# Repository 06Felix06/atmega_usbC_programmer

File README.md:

# ATmega USB-C Programmer

**A small USB-C tool for your own ATmega boards (ATmega328P, ATmega2560, ...). It burns the Arduino bootloader and uploads sketches through a single 2×4 pin header, so your PCBs don't need a USB chip.**

## The idea

If you design your own boards around a bare ATmega chip, for example the ATmega328P from the Arduino Uno/Nano or the ATmega2560 from the Arduino Mega, you normally have two annoying options:

- Put a full USB-to-serial circuit (CH340, USB connector, auto-reset) on **every** board. This costs space, money and adds more things that can go wrong.
- Or burn the bootloader with an Arduino Nano and a bunch of jumper wires, and then use a separate USB-serial adapter for every upload.

This programmer combines both jobs in one small device:

1. **Bootloader mode:** The programmer acts as an *Arduino as ISP* and burns the Arduino bootloader onto a brand-new ATmega through the SPI pins.
2. **Program mode:** The programmer's own microcontroller is switched out of the circuit, and the USB-serial converter is connected directly to the target chip. **Programmer + target board together behave exactly like a normal Arduino board** (for example a Nano with an ATmega328P or a Mega with an ATmega2560). You upload sketches and use the Serial Monitor as usual.

In other words, the Arduino is split in two: the USB part lives in the programmer, and the microcontroller lives on your board. All the target board needs is the ATmega, a resonator or crystal, a few capacitors and one 2×4 pin header.

Switching between the two modes takes four jumpers.

<p align="center"><em>A programmer in its 3D-printed case, plugged onto a second, freshly assembled programmer board to flash its bootloader</em></p>

## Supported microcontrollers

The programmer works with AVR chips that the Arduino IDE supports with a serial (UART) bootloader, for example:

| Target chip | Arduino board to select | Notes |
|---|---|---|
| ATmega328P | Arduino Nano or Arduino Uno | Most common case |
| ATmega2560 | Arduino Mega or Mega 2560 | Bootloader and uploads work the same way |

The programmer itself is always built around an ATmega328P, no matter which chip is on the target board.

## Features

- USB-C connector with a CH340C USB-to-serial converter
- ATmega328P-AU with 16 MHz resonator, running the standard *ArduinoISP* sketch
- One 8-pin connector to the target for both bootloader burning and code upload
- The programmer powers the target board with 5 V over the same connector
- Auto-reset over DTR, so uploads work just like on a regular Arduino board
- LEDs for power, RX, TX and a test LED
- Small 2-layer board (approx. 57 × 25 mm), all parts hand-solderable (0805, SOIC, TQFP)
- 3D-printable case with a window over the mode jumpers

## How it works

```mermaid
flowchart LR
    PC["PC<br/>(Arduino IDE)"] -- USB-C --> CH["CH340C<br/>USB-Serial"]
    CH -- "Bootloader mode<br/>TX / RX / DTR" --> MCU["Programmer ATmega328P<br/>(ArduinoISP)"]
    MCU -- "SPI: D11 / D12 / D13<br/>RESET: D10" --> T["Target ATmega328P<br/>(your board)"]
    CH -. "Program mode<br/>TX / RX / DTR" .-> T
```

The four 3-pin jumpers decide where the CH340's signals go:

| Jumper | Signal | Bootloader position | Program position |
|---|---|---|---|
| J3 | CH340 RXD | → programmer ATmega TX | → target TX |
| J4 | CH340 TXD | → programmer ATmega RX | → target RX |
| J5 | DTR auto-reset | → programmer ATmega RESET | → target RESET |
| J6 | Target RESET | ← programmer pin D10 (ISP reset) | ← DTR auto-reset (via J5) |

On the PCB, the **Bootloader** position is the two pins *away* from the square pad (pins 2–3) and the **Program** position is the two pins *next to* the square pad (pins 1–2). Always move all four jumpers together.

The SPI lines (programmer pins D11–D13) stay connected to the target in both modes. This is not a problem, because the ArduinoISP sketch keeps them as inputs whenever it isn't programming.

## Target connector pinout

Put this 2×4 male pin header (2.54 mm) on your own board. It has the same pinout and footprint as `J2` on the programmer, so the easiest way is to copy that footprint from the KiCad project.

```
          ┌───────────┬───────────┐
  pin 1 ● │ GND       │ RESET     │ pin 2
  pin 3   │ MOSI      │ SCK       │ pin 4
  pin 5   │ +5V       │ MISO      │ pin 6
  pin 7   │ TXD       │ RXD       │ pin 8
          └───────────┴───────────┘
```

Which chip pins these are depends on the target:

| Header signal | ATmega328P | ATmega2560 |
|---|---|---|
| MOSI | PB3 (D11) | PB2 (D51) |
| MISO | PB4 (D12) | PB3 (D50) |
| SCK | PB5 (D13) | PB1 (D52) |
| TXD | PD1 (D1) | PE1 (D1, TXD0) |
| RXD | PD0 (D0) | PE0 (D0, RXD0) |
| RESET | PC6 | RESET |

For the ATmega2560, use the first serial port (UART0), because the Arduino bootloader listens there.

TX and RX are already crossed inside the programmer, so connect the header's TXD to the ATmega's TXD pin and RXD to RXD.

### Design tips for your target board

These are rules I learned the hard way while making several boards with this programmer:

- **Mark pin 1 (GND)** next to the header with a clear dot on the silkscreen. If the programmer is plugged in the wrong way round, 5 V ends up on a signal pin.
- **Place the header so that the GND row faces the edge of the board**, so the programmer (and its case) doesn't hit other parts.
- **Use 16 MHz** (the Arduino bootloaders expect it) and mind the difference between parts: crystal, oscillator and resonator are all different. For the ATmega328P, a ceramic resonator like the Murata `CSTNE16M0V53Z000R0` ([LCSC C783275](https://www.lcsc.com/product-detail/Ceramic-Resonators_Murata-Electronics-CSTNE16M0V53Z000R0_C783275.html)) has the load capacitors built in, needs only three pads and is very small. A crystal needs two extra load capacitors.
- Add a **10 kΩ pull-up on RESET**. You don't need a DTR capacitor on the target, because it's already on the programmer.
- Use the usual decoupling: 100 nF close to every VCC pin, AVCC connected to 5 V and 100 nF from AREF to GND. The ATmega2560 has several VCC/GND pairs, and each one needs its own capacitor.
- The programmer's own ATmega328P circuit (see schematic) is a good, tested reference design you can copy.

## Usage

### Arduino IDE settings

Tested with Arduino IDE 2.3. The board you select always has to match the chip you are talking to:

| Situation | Board | Processor |
|---|---|---|
| Uploading ArduinoISP **to the programmer itself** | Arduino Nano | ATmega328P (Old Bootloader) |
| Target with ATmega328P | Arduino Nano | ATmega328P (Old Bootloader) |
| Target with ATmega2560 | Arduino Mega or Mega 2560 | ATmega2560 (Mega 2560) |

For burning the bootloader, also set **Tools → Programmer → Arduino as ISP**.

### Burning the bootloader onto a new board

1. Set all four jumpers to **Bootloader**.
2. Connect the programmer to the PC, select *Arduino Nano / ATmega328P (Old Bootloader)*, open **File → Examples → 11.ArduinoISP → ArduinoISP** and upload it **to the programmer** like a normal sketch. You only need to do this once, and after that the sketch stays on the programmer.
3. Plug the programmer onto the 8-pin header of the target board (watch the pin-1 marking).
4. Select the board and processor of the **target** (see table above) and **Tools → Programmer → Arduino as ISP**, then click **Tools → Burn Bootloader** and wait until it finishes. On the ATmega2560 this takes a bit longer.
5. Set **Tools → Programmer** back to the default (*AVRISP mkII*) so normal uploads don't accidentally go through the ISP.

### Uploading sketches

1. Set all four jumpers to **Program**.
2. Plug the programmer onto the target board, connect it over USB and select the board that matches the target chip.
3. Upload sketches normally with **Upload** (not "Upload using programmer"). The Serial Monitor talks to the target as well.

If an upload fails with a *"not in sync"* error, first check the board and processor setting (for the ATmega328P: *Old Bootloader*). If it still fails, press the reset button of the target board right when the IDE starts uploading.

### Setting up a brand-new programmer

A freshly assembled programmer has a blank ATmega and needs a bootloader itself. Use a second, already working programmer of this type (or any *Arduino as ISP* setup) for that:

1. Set **all jumpers of the new programmer** to **Bootloader**.
2. Plug the working programmer (jumpers on Bootloader, ArduinoISP uploaded) onto the **`Bootl/CodeUP`** header (`J2`) of the new board, as in the photo above.
3. Burn the bootloader as described above.
4. Unplug the working programmer, connect the new one directly over USB and upload [`firmware/selftest_blink`](firmware/selftest_blink). If the test LED blinks and the counter shows up in the Serial Monitor, the board works.
5. Upload the ArduinoISP sketch onto it, and it's ready to use.

## Hardware

| | |
|---|---|
| Schematic | [`hardware/Atmega_Programmer_Schematic.pdf`](hardware/Atmega_Programmer_Schematic.pdf) |
| KiCad project (KiCad 7 or newer) | [`hardware/`](hardware) |
| Interactive BOM (open in a browser) | [`hardware/ibom.html`](hardware/ibom.html) |
| Gerber + drill files | [`hardware/production/atmega-usb-c-programmer_gerbers.zip`](hardware/production/atmega-usb-c-programmer_gerbers.zip) |
| BOM / pick-and-place for JLCPCB assembly | [`hardware/production/bom.csv`](hardware/production/bom.csv), [`positions.csv`](hardware/production/positions.csv) |

### Bill of materials

| Ref | Part | Package | Qty |
|---|---|---|---|
| U2 | ATmega328P-AU (LCSC C14877) | TQFP-32 | 1 |
| U1 | CH340C (LCSC C84681), no external crystal needed | SOIC-16 | 1 |
| X1 | 16 MHz ceramic resonator CSTNE16M0V53Z000R0 (LCSC C783275) | 3-pin SMD | 1 |
| J7 | USB-C receptacle HRO TYPE-C-31-M-12 (USB 2.0) | SMD | 1 |
| SW1 | Tactile switch 6×6 mm (LCSC C2909692) | SMD | 1 |
| C1, C3, C4, C12 | 100 nF | 0805 | 4 |
| C2, C6, C11 | 10 µF | 0805 | 3 |
| C5, C9 | 1 µF | 0805 | 2 |
| R4 | 10 kΩ | 0805 | 1 |
| R1, R2 | 5.1 kΩ (USB-C CC pull-downs) | 0805 | 2 |
| R5–R8 | 1 kΩ | 0805 | 4 |
| D1, D2 | LED red (RX, TX) | 0805 | 2 |
| D3 | LED green (power) | 0805 | 1 |
| D4 | LED (test LED on D3) | 0805 | 1 |
| J1 | Pin socket 2×4, 2.54 mm (to target) | THT | 1 |
| J2 | Pin header 2×4, 2.54 mm (to program the programmer) | THT | 1 |
| J3–J6 | Pin header 1×3, 2.54 mm + jumper | THT | 4 |

### Design notes

- **DTR capacitor:** The auto-reset capacitor between the CH340's DTR pin and RESET (C2) is **10 µF instead of the usual 100 nF**. This turned out to be important for uploads to work, and it was changed in revision 1.1.
- The CH340's RX and TX are deliberately crossed in the schematic labels (`TXout` is the CH340's RXD input), so the jumpers connect straight through to the ATmega pins.
- Both USB-C CC pins have their own 5.1 kΩ pull-down, so the board also works with USB-C to USB-C cables and chargers.
- The USB data lines (D+/D−) are kept as short as possible.
- There is no fuse or reverse-polarity protection on the 5 V line. The target gets USB power directly.

## Enclosure

The 3D-printable case consists of a bottom part, a lid with a window over the mode jumpers and a small cap for the reset button.

| | |
|---|---|
| Ready-to-print STL files | [`enclosure/stl/`](enclosure/stl) |
| Editable Fusion model | [`enclosure/fusion/ATmega_Programmer_Case.f3d`](enclosure/fusion/ATmega_Programmer_Case.f3d) |

In the Fusion model, the bodies are named `Case_Lid`, `Case_Bottom` and `Reset_Button_Cap`. The sketches are prefixed with the part they belong to (`Lid_..`, `Bottom_..`). A hidden `PCB_Reference` body shows the board outline, so you can adapt the case if you change the PCB.

Tip: Small labels "Bootloader" and "Program" next to the window make it obvious which way the jumpers have to go.

## Repository structure

```
├── docs/images/          Pictures for this README
├── enclosure/
│   ├── fusion/           Editable Fusion model (.f3d)
│   └── stl/              Ready-to-print STL files
├── firmware/
│   └── selftest_blink/   Test sketch for a freshly assembled programmer
└── hardware/
    ├── Atmega_Programmer.kicad_pro / .kicad_sch / .kicad_pcb
    ├── Atmega_Programmer_Schematic.pdf
    ├── ibom.html          Interactive BOM / assembly helper
    └── production/        Gerbers, BOM and pick-and-place files
```

The programmer itself runs the unmodified **ArduinoISP** example that comes with the Arduino IDE, so no custom firmware is needed.

## Changelog

- **Rev 1.1 (March 2025):** DTR auto-reset capacitor changed from 100 nF to 10 µF for reliable uploads.
- **Rev 1.0 (November 2024):** First version.

## License

This project is licensed under [Creative Commons Attribution-NonCommercial 4.0 International (CC BY-NC 4.0)](https://creativecommons.org/licenses/by-nc/4.0/). You may build, modify and share it for non-commercial purposes, as long as you give credit. See [LICENSE](LICENSE).

Designed by Felix Steck.

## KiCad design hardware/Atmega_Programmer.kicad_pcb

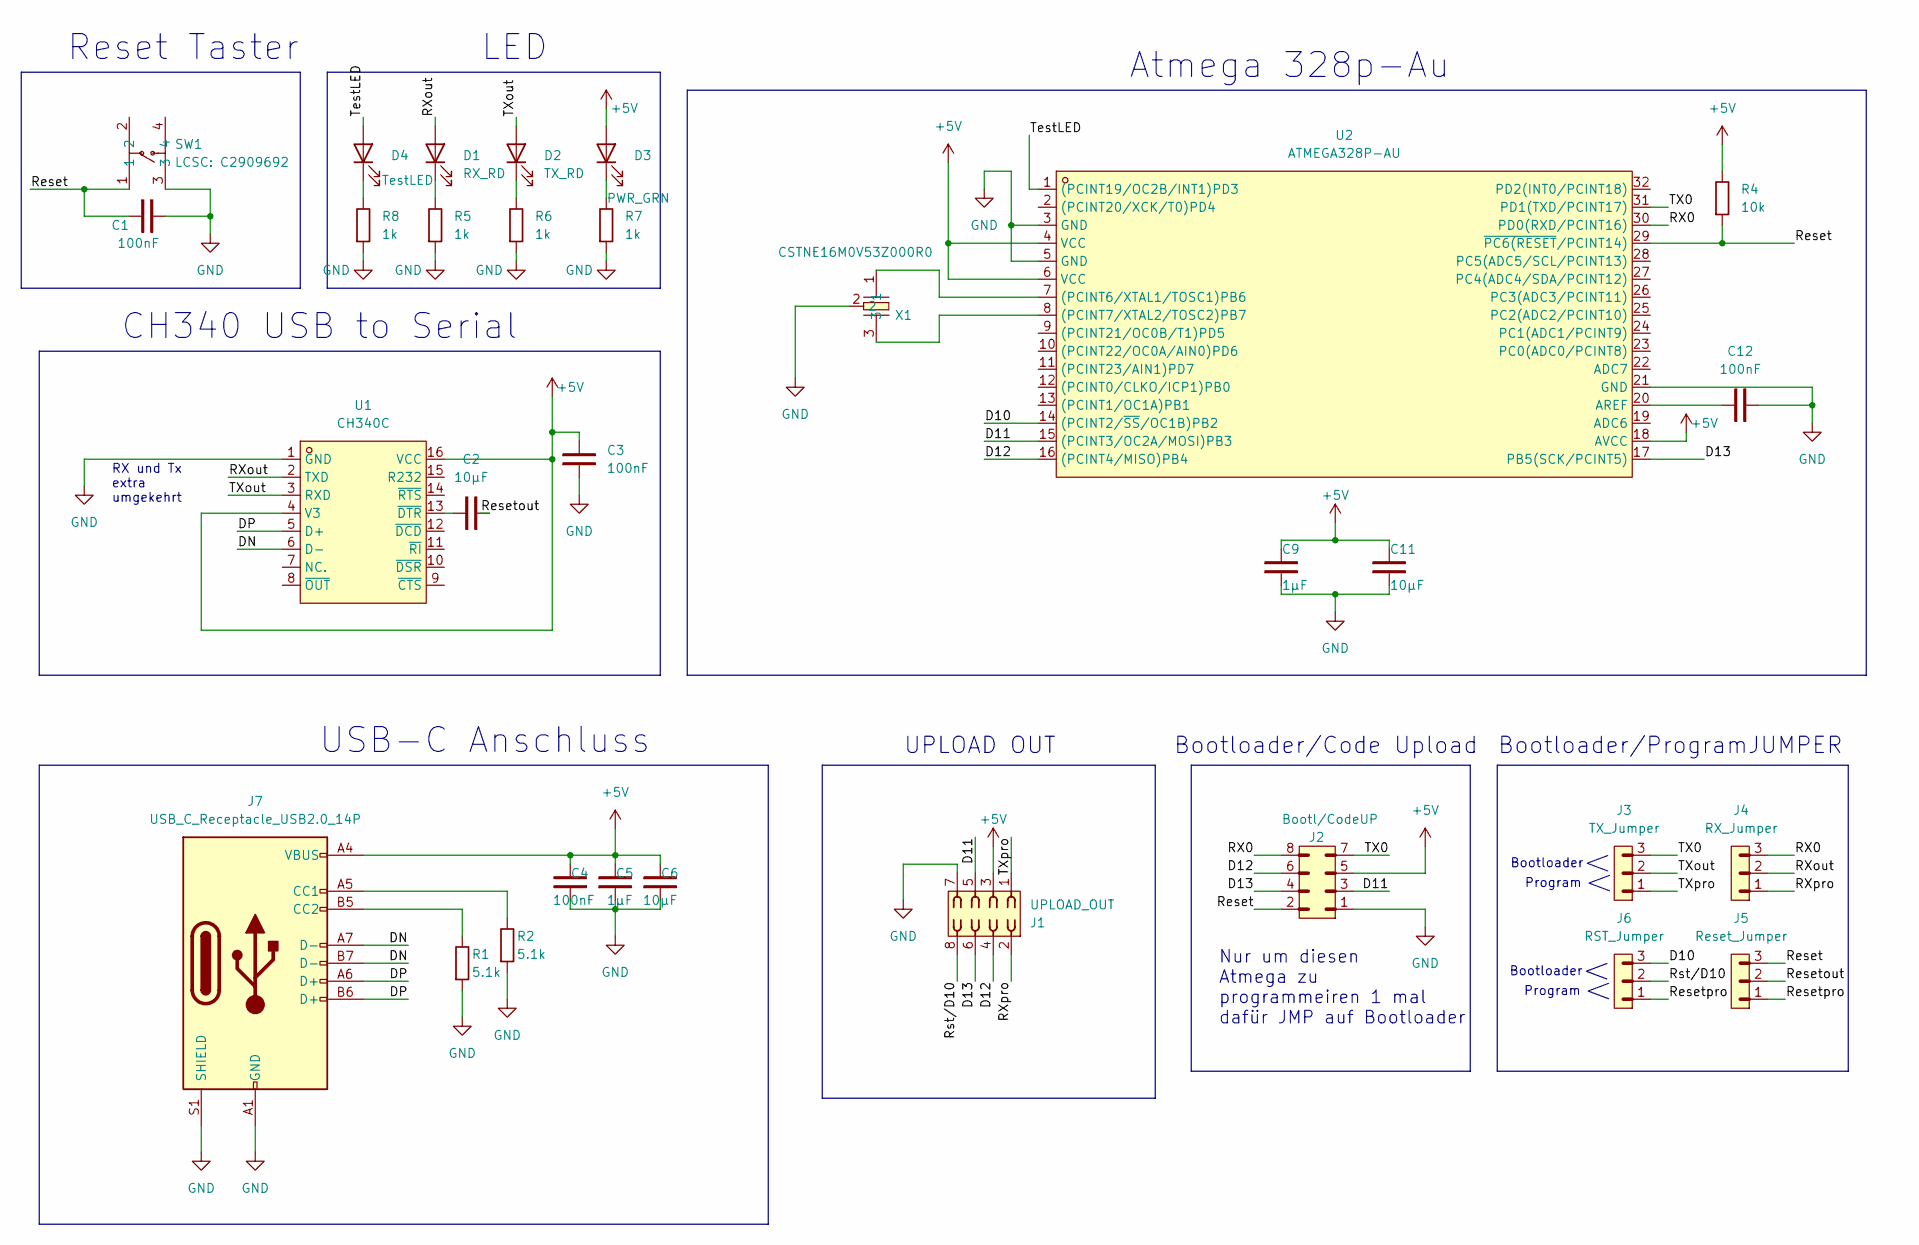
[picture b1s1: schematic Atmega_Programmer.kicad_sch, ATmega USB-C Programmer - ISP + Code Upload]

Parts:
C1, C3, C4, C12: 100nF; C_0805_2012Metric
C2, C6, C11: 10µF; C_0805_2012Metric
C5, C9: 1µF; C_0805_2012Metric
D1: RX_RD; LED_0805_2012Metric
D2: TX_RD; LED_0805_2012Metric
D3: PWR_GRN; LED_0805_2012Metric
D4: TestLED; LED_0805_2012Metric
J1: UPLOAD_OUT; PinSocket_2x04_P2.54mm_Vertical
J2: Bootl/CodeUP; PinHeader_2x04_P2.54mm_Vertical
J3: TX_Jumper; PinHeader_1x03_P2.54mm_Vertical
J4: RX_Jumper; PinHeader_1x03_P2.54mm_Vertical
J5: Reset_Jumper; PinHeader_1x03_P2.54mm_Vertical
J6: RST_Jumper; PinHeader_1x03_P2.54mm_Vertical
J7: USB_C_Receptacle_USB2.0_14P; USB_C_Receptacle_HRO_TYPE-C-31-M-12
R1, R2: 5.1k; R_0805_2012Metric
R4: 10k; R_0805_2012Metric
R5, R6, R7, R8: 1k; R_0805_2012Metric
SW1: LCSC: C2909692; SW-SMD_4P-L6.2-W6.2-P4.50-LS8.6; LCSC Part C2909692
U1: CH340C; SOP-16_L10.0-W3.9-P1.27-LS6.0-BL; LCSC Part C84681
U2: ATMEGA328P-AU; TQFP-32_L7.0-W7.0-P0.80-LS9.0-BL; LCSC Part C14877
X1: CSTNE16M0V53Z000R0; OSC-SMD_3P-L3.2-W1.3-P1.20-L; LCSC Part C783275

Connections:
+5V: C3.2, C4.1, C5.2, C6.2, C9.2, C11.2, D3.2 (A), J1.3, J2.5, J7.A4 (VBUS), J7.A9 (VBUS), J7.B4 (VBUS), J7.B9 (VBUS), R4.2, U1.4 (V3), U1.16 (VCC), U2.4 (VCC), U2.6 (VCC), U2.18 (AVCC)
/D10: J6.3, U2.14 ((PCINT2/~SS/OC1B)PB2)
/D11: J1.5, J2.3, U2.15 ((PCINT3/OC2A/MOSI)PB3)
/D12: J1.4, J2.6, U2.16 ((PCINT4/MISO)PB4)
/D13: J1.6, J2.4, U2.17 (PB5(SCK/PCINT5))
/DN: J7.A7 (D-), J7.B7 (D-), U1.6 (D-)
/DP: J7.A6 (D+), J7.B6 (D+), U1.5 (D+)
/RX0: J2.8, J4.3, U2.30 (PD0(RXD/PCINT16))
/RXout: D1.2 (A), J4.2, U1.2 (TXD)
/RXpro: J1.2, J4.1
/Reset: C1.1, J2.2, J5.3, R4.1, SW1.1, U2.29 (~PC6(RESET/PCINT14))
/Resetout: C2.1, J5.2
/Resetpro: J5.1, J6.1
/Rst/D10: J1.8, J6.2
/TX0: J2.7, J3.3, U2.31 (PD1(TXD/PCINT17))
/TXout: D2.2 (A), J3.2, U1.3 (RXD)
/TXpro: J1.1, J3.1
/TestLED: D4.2 (A), U2.1 ((PCINT19/OC2B/INT1)PD3)
GND: C1.2, C3.1, C4.2, C5.1, C6.1, C9.1, C11.1, C12.1, J1.7, J2.1, J7.A1 (GND), J7.A12 (GND), J7.B1 (GND), J7.B12 (GND), J7.S1 (SHIELD), R1.1, R2.1, R5.1, R6.1, R7.1, R8.1, SW1.3, U1.1 (GND), U2.3 (GND), U2.5 (GND), U2.21 (GND), X1.2
unnamed: D1.1 (K), R5.2
unnamed: D2.1 (K), R6.2
unnamed: D3.1 (K), R7.2
unnamed: D4.1 (K), R8.2
unnamed: J7.A5 (CC1), R2.2
unnamed: J7.B5 (CC2), R1.2
unnamed: C2.2, U1.13 (~DTR)
unnamed: U2.7 ((PCINT6/XTAL1/TOSC1)PB6), X1.1
unnamed: U2.8 ((PCINT7/XTAL2/TOSC2)PB7), X1.3
unnamed: C12.2, U2.20 (AREF)

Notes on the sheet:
Reset Taster
CH340 USB to Serial
Atmega 328p-Au
RX und Tx extra umgekehrt
USB-C Anschluss
Nur um diesen Atmega zu programmeiren 1 mal dafür JMP auf Bootloader
UPLOAD OUT
Bootloader
Bootloader/ProgramJUMPER
Bootloader/Code Upload
LED
Program

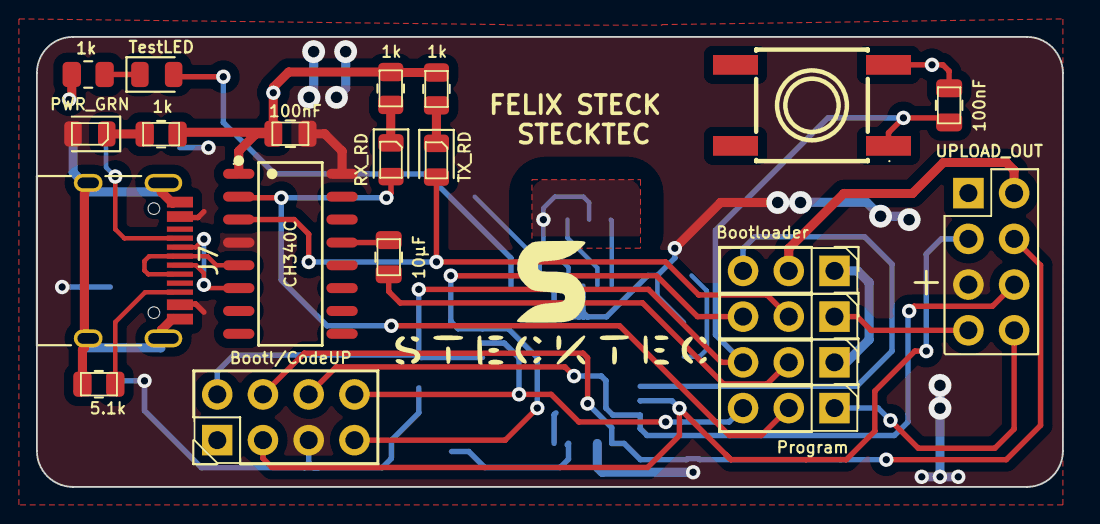
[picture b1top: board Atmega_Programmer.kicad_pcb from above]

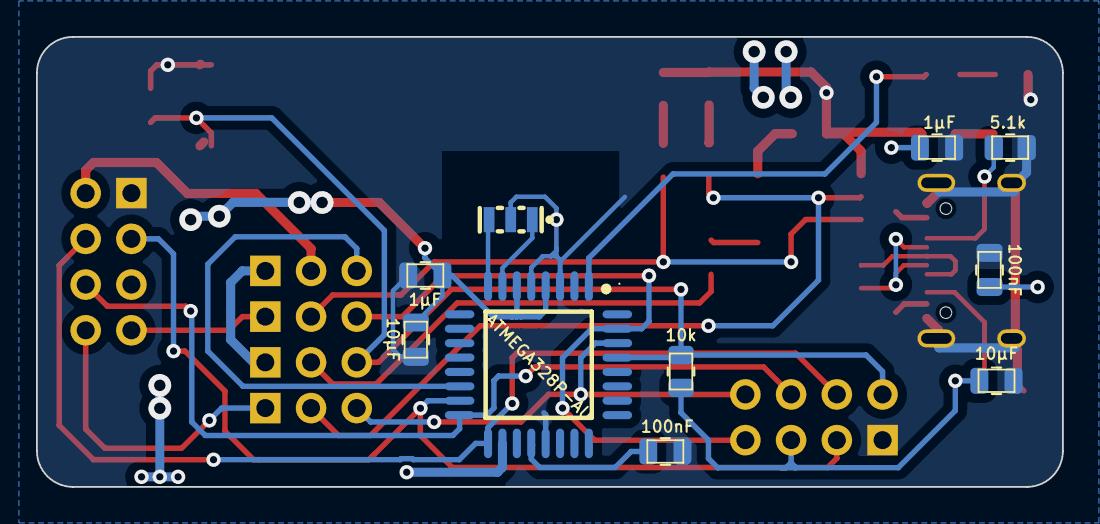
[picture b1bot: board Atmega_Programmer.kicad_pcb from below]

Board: 2 copper layers, 57.0 x 25.0 mm, 31 parts (10 on the bottom side), 29 nets.

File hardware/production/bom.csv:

Designator,Footprint,Quantity,Value,LCSC Part #
"C1, C12, C3, C4",0805,4,100nF,
"C11, C2, C6",0805,3,10µF,
"C5, C9",0805,2,1µF,
D1,0805,1,RX_RD,
D2,0805,1,TX_RD,
D3,0805,1,PWR_GRN,
D4,0805,1,TestLED,
J1,PinSocket_2x04_P2.54mm_Vertical,1,UPLOAD_OUT,
J2,PinHeader_2x04_P2.54mm_Vertical,1,Bootl/CodeUP,
J3,PinHeader_1x03_P2.54mm_Vertical,1,TX_Jumper,
J6,PinHeader_1x03_P2.54mm_Vertical,1,RST_Jumper,
J4,PinHeader_1x03_P2.54mm_Vertical,1,RX_Jumper,
J5,PinHeader_1x03_P2.54mm_Vertical,1,Reset_Jumper,
J7,USB_C_Receptacle_HRO_TYPE-C-31-M-12,1,USB_C_Receptacle_USB2.0_14P,
"R1, R2",0805,2,5.1k,
R4,0805,1,10k,
"R5, R6, R7, R8",0805,4,1k,
SW1,SW-SMD_4P-L6.2-W6.2-P4.50-LS8.6,1,LCSC: C2909692,C2909692
U1,SOP-16_L10.0-W3.9-P1.27-LS6.0-BL,1,CH340C,C84681
U2,TQFP-32_L7.0-W7.0-P0.80-LS9.0-BL,1,ATMEGA328P-AU,C14877
X1,OSC-SMD_3P-L3.2-W1.3-P1.20-L,1,CSTNE16M0V53Z000R0,C783275
